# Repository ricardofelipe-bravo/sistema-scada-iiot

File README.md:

# Sistema SCADA con Nodo Edge IIoT — Monitor de Variables Eléctricas

Sistema de monitoreo industrial en tiempo real que integra un nodo Edge basado en **ESP32**, comunicación segura **MQTT/TLS**, protocolo industrial **Modbus TCP** y un dashboard **SCADA web** desarrollado con Python y Flask. Diseñado para supervisión de variables eléctricas en motores industriales con detección automática de alarmas y notificaciones por email.

---

## Arquitectura del Sistema

```
ESP32 (Nodo Edge)
  │  WiFi + Portal Cautivo
  │  MQTT/TLS — HiveMQ Cloud (puerto 8883)
  ▼
Python — monitor.py
  │  Suscriptor MQTT
  ├── SQLite (histórico de mediciones)
  ├── Alertas Email (SMTP — flanco ascendente)
  └── Flask — app.py
          │  API REST
          ▼
    Dashboard Web
    Chart.js — tiempo real
    Gauges + Gráficas + Historial de alarmas
```

---

## Características

- **Nodo Edge ESP32** con portal cautivo para configuración WiFi sin reprogramar, sincronización horaria NTP y LEDs indicadores de estado
- **Dos versiones de firmware** — producción con sensor PZEM-004T y simulación para pruebas sin hardware
- **Comunicación MQTT/TLS** sobre HiveMQ Cloud con publicación de JSON estructurado cada 2 segundos
- **Dashboard SCADA web** con gauges estilo velocímetro, gráficas de tendencia en tiempo real, panel de alarmas y historial de eventos
- **Base de datos SQLite** para almacenamiento histórico de mediciones
- **Sistema de alarmas** con detección por flanco ascendente y notificación automática por email
- **PCB diseñada en KiCad 8** para integración con sensor PZEM-004T
- Arquitectura preparada para conexión con **PLC vía Modbus TCP**

---

## Firmware ESP32 — Dos Versiones

### `nodo_edge_iiot_sensor.ino` — Producción (con PZEM-004T)
Versión para uso con hardware real. Lee voltaje, corriente, potencia activa, energía acumulada, frecuencia y factor de potencia directamente del sensor PZEM-004T. Detecta automáticamente si el sensor no responde.

### `nodo_edge_iiot_simulacion.ino` — Simulación (sin sensor)
Versión para pruebas del sistema completo sin hardware de medición. Simula un motor industrial 1HP / 220V con comportamiento realista — arranque, carga nominal, calentamiento gradual y generación de alarmas.

---

## Portal Cautivo — Configuración WiFi

El ESP32 incluye un portal cautivo que permite configurar la red WiFi sin necesidad de reprogramar el dispositivo.

### Cómo funciona

**Primera vez (sin credenciales guardadas):**

1. El ESP32 enciende y no encuentra red WiFi configurada
2. Crea automáticamente una red WiFi propia:
   - **Red:** `NodoEdge_Config`
   - **Contraseña:** `nodo1234`
3. Conéctate a esa red desde tu celular o computador
4. Se abre automáticamente una página de configuración en `192.168.4.1`
5. Selecciona tu red WiFi e ingresa la contraseña
6. El ESP32 guarda las credenciales y se conecta

**Siguiente encendido:**
- El ESP32 se conecta automáticamente sin mostrar el portal

**Si necesitas cambiar la red:**
- Mantén presionado el botón RESET por 10 segundos para borrar credenciales
- El portal cautivo se activa de nuevo

### Indicadores LED durante el portal
| LED | Estado | Significado |
|---|---|---|
| WiFi (GPIO23) | Parpadeo rápido | Portal cautivo activo |
| WiFi (GPIO23) | Fijo encendido | WiFi conectado |
| MQTT (GPIO22) | Fijo encendido | HiveMQ conectado |
| Alarma (GPIO21) | Fijo encendido | Variable fuera de rango |

---

## Conexión PZEM-004T al ESP32

```
PZEM-004T          ESP32 DevKit 38 pines
─────────          ──────────────────────
VCC (5V)    →      VIN  (pin 19)
GND         →      GND  (pin 14)
TX          →      GPIO16 / RX2  (pin 28)
RX          →      GPIO17 / TX2  (pin 29)
```

> **Importante:** El PZEM-004T trabaja con 220V en su lado de medición. Maneja las conexiones de alta tensión con precaución.

---

## Variables Monitoreadas

| Variable | Unidad | Rango normal | Umbral de alarma |
|---|---|---|---|
| Voltaje de línea | V | 200 – 240 | > 228 V |
| Corriente de carga | A | 0 – 6 | > 5 A |
| Potencia activa | W | calculada | — |
| Factor de potencia | — | 0.75 – 0.95 | — |
| Temperatura | °C | 25 – 65 | > 65 °C |
| Energía acumulada | kWh | — | — |
| Frecuencia | Hz | 59 – 61 | — |

---

## Stack Tecnológico

### Firmware ESP32
| Librería | Autor | Función |
|---|---|---|
| WiFiManager | tzapu | Portal cautivo para configuración WiFi |
| PubSubClient | Nick O'Leary | Cliente MQTT |
| ArduinoJson | Benoit Blanchon | Serialización JSON |
| PZEM004Tv30 | Jakub Mandula | Lectura sensor PZEM-004T |
| WiFiClientSecure | ESP32 built-in | Conexión TLS/SSL |
| time.h | ESP32 built-in | Sincronización NTP |

### Backend Python
| Librería | Función |
|---|---|
| paho-mqtt | Suscripción al broker MQTT |
| flask | Servidor web y API REST |
| sqlite3 | Base de datos histórica |
| smtplib | Envío de alertas por email |

### Frontend
| Tecnología | Función |
|---|---|
| Chart.js | Gráficas de tendencia en tiempo real |
| HTML/CSS/JS | Dashboard SCADA responsivo |
| SVG | Gauges estilo velocímetro animados |

---

## Estructura del Proyecto

```
sistema-scada-iiot/
│
├── monitor.py                          # Suscriptor MQTT + SQLite + alertas email
├── app.py                              # Servidor Flask + API REST
├── .gitignore
│
├── templates/
│   └── index.html                      # Dashboard SCADA
│
├── static/
│   └── chart.js                        # Librería Chart.js (local)
│
├── nodo_edge_iiot.ino/
│   ├── nodo_edge_iiot_sensor.ino       # Firmware producción (PZEM-004T)
│   └── nodo_edge_iiot_simulacion.ino   # Firmware simulación (pruebas)
│
├── pcb/
│   ├── nodo edge IIot.kicad_sch        # Esquemático
│   ├── nodo edge IIot.kicad_pcb        # Layout PCB
│   └── nodo edge IIot.kicad_pro        # Proyecto KiCad
│
└── docs/
    ├── dashboard_motor_off.jpg         # Dashboard — motor apagado
    ├── dashboard_motor_on.jpg          # Dashboard — motor encendido
    └── dashboard_alarma.jpg            # Dashboard — alarma activa
```

---

## Cómo Correr el Proyecto

### Requisitos Python
```bash
pip install flask paho-mqtt
```

### 1. Iniciar el monitor MQTT
```bash
python monitor.py
```

### 2. Iniciar el servidor web
```bash
python app.py
```

### 3. Abrir el dashboard
```
http://127.0.0.1:5000
```

### 4. Publicar datos de prueba desde HiveMQ
Topic: `industrial/motor/variables`

**Motor apagado:**
```json
{"voltaje":219.8,"corriente":0.3,"potencia":55.2,"factor_potencia":0.92,"temperatura":25.0,"estado_motor":0,"timestamp":"2026-06-05 10:00:00"}
```

**Motor encendido:**
```json
{"voltaje":220.5,"corriente":4.5,"potencia":773.6,"factor_potencia":0.78,"temperatura":42.3,"estado_motor":1,"timestamp":"2026-06-05 10:01:00"}
```

**Alarma de temperatura:**
```json
{"voltaje":221.2,"corriente":4.8,"potencia":826.4,"factor_potencia":0.78,"temperatura":68.5,"estado_motor":1,"timestamp":"2026-06-05 10:02:00"}
```

---

---

## Configuración HiveMQ Cloud

HiveMQ Cloud es el broker MQTT que recibe los datos del ESP32 y los entrega a Python.

### Crear cuenta y cluster gratuito

1. Ve a [console.hivemq.cloud](https://console.hivemq.cloud)
2. Crea una cuenta gratuita
3. Click en **"Create new cluster"** → selecciona plan **Free**
4. Elige la región más cercana (US East o EU)
5. Espera que el cluster esté activo (~1 minuto)

### Crear credenciales de acceso

1. Dentro del cluster ve a **"Access Management"**
2. Click en **"Add new credentials"**
3. Crea un usuario y contraseña — guárdalos
4. Permiso: **Publicar y Suscribirse**
5. Click en **Guardar**

### Datos de conexión

Una vez creado el cluster, en la página principal encuentras:

| Parámetro | Dónde encontrarlo | Ejemplo |
|---|---|---|
| Host | Página principal del cluster | `xxxx.s1.eu.hivemq.cloud` |
| Puerto TLS | Siempre es 8883 | `8883` |
| Usuario | Access Management | el que creaste |
| Contraseña | Access Management | la que creaste |

### Actualizar credenciales en el firmware

En el archivo `.ino` busca estas líneas y reemplaza con tus datos:

```cpp
const char* MQTT_HOST = "TU_HOST.s1.eu.hivemq.cloud";
const char* MQTT_USER = "tu_usuario";
const char* MQTT_PASS = "tu_contraseña";
```

### Actualizar credenciales en Python

En `monitor.py` busca:

```python
MQTT_HOST = "TU_HOST.s1.eu.hivemq.cloud"
MQTT_USER = "tu_usuario"
MQTT_PASS = "tu_contraseña"
```

### Probar la conexión desde el cliente web

1. En tu consola HiveMQ ve a la pestaña **"Cliente web"**
2. Conecta con tus credenciales
3. Publica un JSON al topic `industrial/motor/variables`
4. Verifica que `monitor.py` lo recibe en la terminal

---

## PCB — Nodo Edge IIoT

Diseñada en **KiCad 8** para montaje del nodo de medición de variables eléctricas.

### Componentes

| Componente | Referencia | Función |
|---|---|---|
| ESP32 DevKit 38 pines | U1 | Controlador principal |
| PZEM-004T | J1 | Sensor de variables eléctricas |
| LED verde | D1 | Indicador WiFi (GPIO23) |
| LED azul | D2 | Indicador MQTT (GPIO22) |
| LED rojo | D3 | Indicador Alarma (GPIO21) |
| Resistencias 330Ω | R1, R2, R3 | Limitación corriente LEDs |
| Condensador 100µF | C1 | Filtrado alimentación |
| Condensador 100nF | C2 | Desacople alta frecuencia |
| DC Jack 5V | J2 | Entrada de alimentación |

### Alimentación

```
Adaptador 5V DC
      │
   DC Jack
      │
   ESP32 VIN (pin 19) ──── PZEM-004T VCC
      │
   ESP32 interno 3.3V ──── lógica interna
```

### Archivos KiCad en carpeta `pcb/`

| Archivo | Contenido |
|---|---|
| `.kicad_sch` | Esquemático completo con conexiones |
| `.kicad_pcb` | Layout de la PCB con ruteo |
| `.kicad_pro` | Proyecto KiCad con configuración |

> Los archivos pueden abrirse directamente con **KiCad 8.0** disponible en [kicad.org](https://www.kicad.org)

## Capturas del Dashboard

### Motor apagado — operación normal

### Motor encendido — carga nominal

### Alarma activa — sobretemperatura

---

## Autor

**Ricardo Felipe Bravo**  
Ingeniero Electrónico — Universidad de Nariño  
Orientado al sector eléctrico e industrial

📩 ricardofelipebravo12@gmail.com  
🔗 [LinkedIn](https://www.linkedin.com/in/ricardofelipe-bravo)

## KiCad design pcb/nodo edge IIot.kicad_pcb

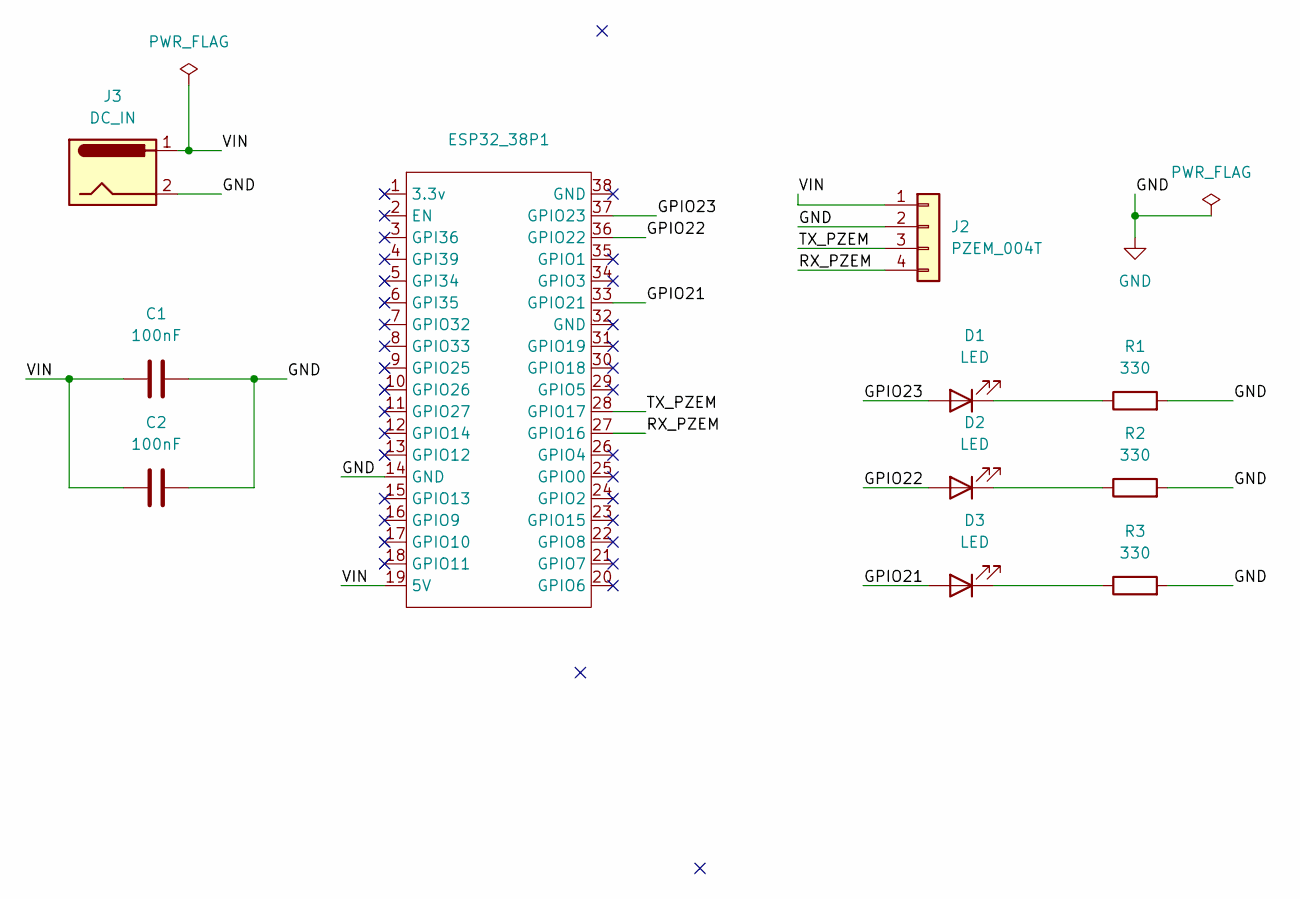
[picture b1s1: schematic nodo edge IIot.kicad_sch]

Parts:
C1, C2: 100nF; C_Disc_D5.0mm_W2.5mm_P5.00mm
D1, D2, D3: LED; LED_D3.0mm
ESP32_38P1: ESP32-38pin
J2: PZEM_004T; PinHeader_1x04_P2.54mm_Vertical
J3: DC_IN; BarrelJack_Horizontal
R1, R2, R3: 330; R_Axial_DIN0207_L6.3mm_D2.5mm_P7.62mm_Horizontal

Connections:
/GPIO21: D3.2 (A), ESP32_38P1.33 (GPIO21)
/GPIO22: D2.2 (A), ESP32_38P1.36 (GPIO22)
/GPIO23: D1.2 (A), ESP32_38P1.37 (GPIO23)
/RX_PZEM: ESP32_38P1.27 (GPIO16), J2.4
/TX_PZEM: ESP32_38P1.28 (GPIO17), J2.3
/VIN: C1.1, C2.1, ESP32_38P1.19 (5V), J2.1, J3.1
GND: C1.2, C2.2, ESP32_38P1.14 (GND), J2.2, J3.2, R1.2, R2.2, R3.2
unnamed: D1.1 (K), R1.1
unnamed: D2.1 (K), R2.1
unnamed: D3.1 (K), R3.1

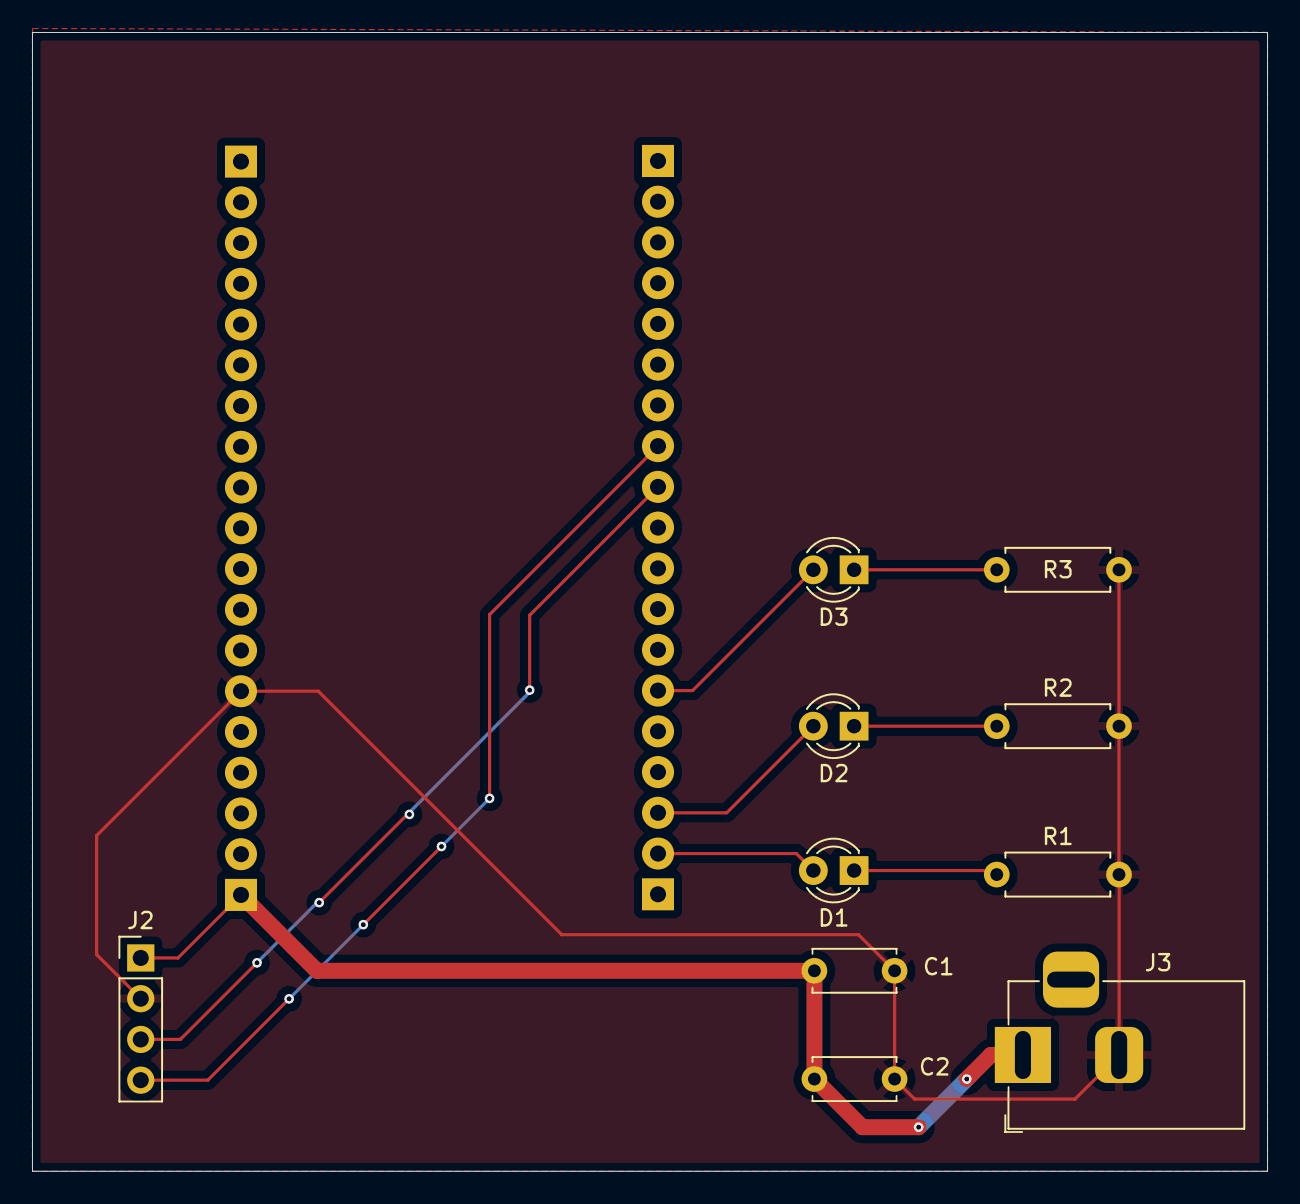
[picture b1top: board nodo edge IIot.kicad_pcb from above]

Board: 2 copper layers, 77.0 x 71.0 mm, 11 parts (1 on the bottom side), 10 nets.

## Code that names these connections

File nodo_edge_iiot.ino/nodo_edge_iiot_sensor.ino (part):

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 * ============================================================
 * Hardware requerido:
 *   - ESP32 DevKit 38 pines
 *   - Sensor PZEM-004T (conectado a GPIO16/GPIO17)
 *   - LEDs: WiFi (GPIO23), MQTT (GPIO22), Alarma (GPIO21)
 *
 * Librerías requeridas:
 *   - WiFiManager     (tzapu)
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 *   - PZEM004Tv30     (Jakub Mandula)
 *
 * Conexión PZEM-004T:
 *   PZEM TX  →  ESP32 GPIO16 (RX2)
 *   PZEM RX  →  ESP32 GPIO17 (TX2)
 *   PZEM VCC →  ESP32 VIN (5V)
 *   PZEM GND →  ESP32 GND
 *
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
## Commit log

2026-06-05 Initial commit: Sistema SCADA IoT - monitor MQTT, dashboard Flask, firmware ESP32
2026-06-06 Add dashboard, PCB files, firmware, docs and project structure
2026-06-06 Add production firmware (PZEM-004T) and simulation firmware with portal cautivo
2026-06-06 Add professional README with architecture, usage and documentation
2026-06-06 Update README: portal cautivo, firmware versions, PZEM-004T wiring
2026-06-06 Update README: HiveMQ setup guide and PCB components detail
2026-06-06 Add edge processing: local buffer, moving average filter, local alarm detection
2026-06-08 Update PCB design
